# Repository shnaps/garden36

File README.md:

# garden36 🌱

A 36-key wireless split keyboard with Kailh Choc hotswap switches, nice!nano v2 controllers, and nice!view displays.

---

## Features

- **36 keys** — 3×5 column-stagger + 3 thumb keys per half
- **Wireless** — nRF52840 via nice!nano v2, ZMK firmware
- **Hotswap** — Kailh Choc v1 sockets, swap switches without soldering
- **Display** — nice!view MIP display per half (WPM, layer, battery)
- **Battery** — JST-PH LiPo connector + power switch per half
- **Low profile** — Choc spacing, slim build

---

## Gallery

| Top | Bottom |
|-----|--------|
|  |  |

> Photos of the built keyboard coming once V2 is assembled. See `pics/photos/` for updates.

---

## Bill of Materials

Full BOM with source links: [docs/bom.md](docs/bom.md)

| Component | Qty |
|-----------|-----|
| nice!nano v2 | 2 |
| nice!view | 2 |
| Kailh Choc v1 switch | 36 |
| Kailh hotswap socket CPG135001S30 | 36 |
| 1N4148W diode SOD-123 | 36 |
| MSK12C02-HB power switch | 2 |
| B3U-1000P reset button | 2 |
| JST S2B-PH-SM4-TB battery connector | 2 |
| LiPo battery ~110–300 mAh | 2 |
| M2 standoffs + screws | ~28 |
| Choc keycaps | 36 |

---

## PCB

Gerbers and drill files for JLCPCB/PCBWay are in the [latest release](https://github.com/shnaps/garden36/releases/latest).

DXF and SVG edge cuts for laser-cutting plates: [`exports/`](exports/)

---

## Build Guide

Step-by-step assembly instructions: [docs/buildguide.md](docs/buildguide.md)

---

## Firmware

ZMK config: [github.com/shnaps/zmk-config](https://github.com/shnaps/zmk-config)

Flash via UF2 — double-tap reset on each half to enter bootloader, drag-and-drop `.uf2`. See build guide for details.

---

## Case

A **parametric case generator** lives in [`case-gen/`](case-gen/) — it builds
the case (bottom tray, choc switch plate, controller cover) straight from
`garden36.kicad_pcb`, so it always fits the board. Print files in
`case-gen/out/`. See the [case-gen README](case-gen/README.md) for hardware,
parameters, and the in-progress controller-on-bottom redesign.

Older hand-built STEP files remain in [`case/`](case/).

---

## Design History

- **V1** — initial design, 5-column, wired (see [`v1` branch](https://github.com/shnaps/garden36/tree/v1))
- **V2** (current) — redesigned with wireless, nice!view displays, hotswap

---

## Credits

- [marbastlib](https://github.com/ebastler/marbastlib) by ebastler — Choc switch and controller footprints
- [nice!keyboards](https://nicekeyboards.com) — nice!nano and nice!view hardware
- Split keyboard inspiration: [MRIYA](https://github.com/themaxbang/MRIYA), [temper](https://github.com/raeedcho/temper), [urchin](https://github.com/duckyb/urchin)

---

## License

[MIT](LICENSE) © 2025 Viachaslau Ravinski

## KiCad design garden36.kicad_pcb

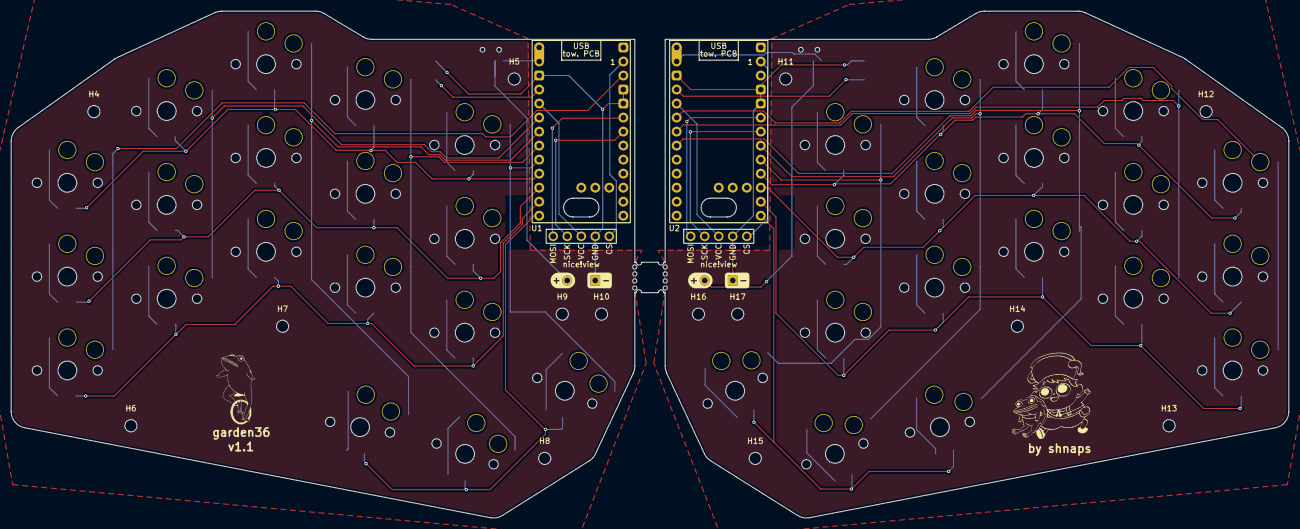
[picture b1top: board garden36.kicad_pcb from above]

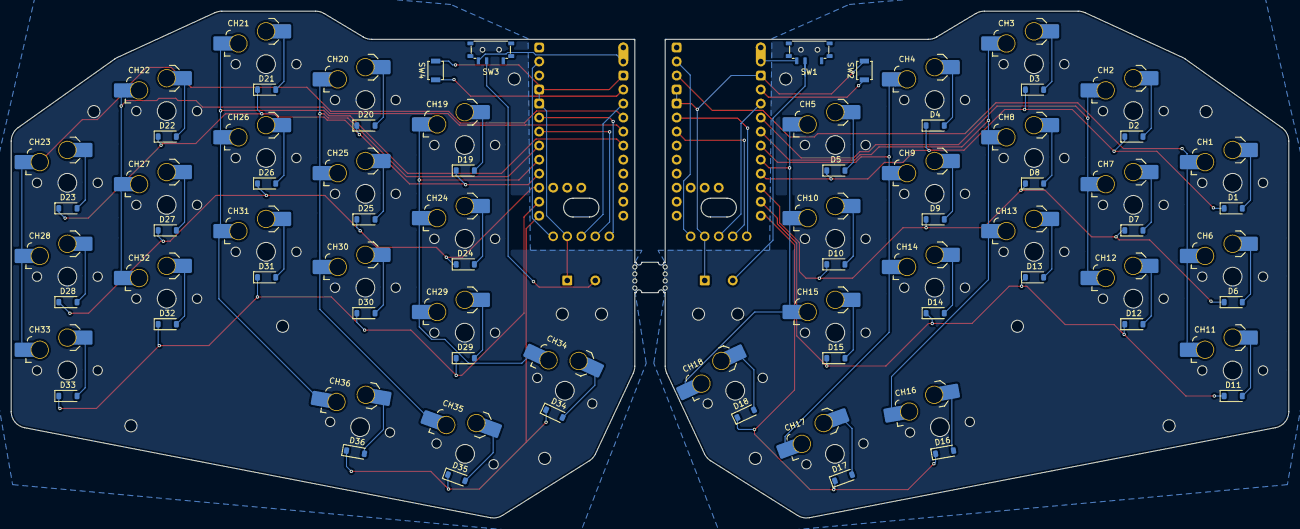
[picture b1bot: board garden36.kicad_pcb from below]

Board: 2 copper layers, 231.5 x 91.8 mm, 100 parts (76 on the bottom side), 70 nets.

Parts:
CH1, CH2, CH3, CH4, CH5, CH6, CH7, CH8, CH9, CH10, CH11, CH12, CH13, CH14, CH15, CH16, CH17, CH18, CH19, CH20, CH21, CH22, CH23, CH24, CH25, CH26, CH27, CH28, CH29, CH30, CH31, CH32, CH33, CH34, CH35, CH36: choc_v1_SW_HS; SW_choc_v1_HS_CPG135001S30_1u
D1, D2, D3, D4, D5, D6, D7, D8, D9, D10, D11, D12, D13, D14, D15, D16, D17, D18, D19, D20, D21, D22, D23, D24, D25, D26, D27, D28, D29, D30, D31, D32, D33, D34, D35, D36: 1N4148W; D_SOD-123
Display1, Display2: nice!view; nice_view
H4, H5, H6, H7, H8, H9, H10, H11, H12, H13, H14, H15, H16, H17: MountingHole; MountingHole_2.2mm_M2
MB4, MB5: mousebites_1mm
PW1, PW2: Battery
SW1, SW3: SW_SPDT; SW_MSK12C02-HB
SW2, SW4: SW_Push; SW_SPST_B3U-1000P
U1, U2: nice_nano; nice_nano_AH_USBdn
by shnaps: LOGO
garden36: LOGO

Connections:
+3.3V: Display1.3 (VCC), U1.16 (3V3)
COL0: CH1.1, CH6.1, CH11.1, U1.2 (P0.08)
COL1: CH2.1, CH7.1, CH12.1, U1.17 (P0.31-LF)
COL2: CH3.1, CH8.1, CH13.1, CH16.1, U1.18 (P0.29-LF)
COL3: CH4.1, CH9.1, CH14.1, CH17.1, U1.19 (P0.02-LF)
COL4: CH5.1, CH10.1, CH15.1, CH18.1, U1.20 (P1.15-LF)
CS: Display1.5 (CS), U1.1 (P0.06)
GND: Display1.4 (GND), PW1.2 (BAT-), SW2.2, U1.3 (GND), U1.4 (GND), U1.14 (GND)
MOSI: Display1.1 (MOSI), U1.5 (P0.17)
unnamed: CH1.2, D1.2 (A)
unnamed: CH2.2, D2.2 (A)
unnamed: CH3.2, D3.2 (A)
unnamed: CH4.2, D4.2 (A)
unnamed: CH5.2, D5.2 (A)
unnamed: CH6.2, D6.2 (A)
unnamed: CH7.2, D7.2 (A)
unnamed: CH8.2, D8.2 (A)
unnamed: CH9.2, D9.2 (A)
unnamed: CH10.2, D10.2 (A)
unnamed: CH11.2, D11.2 (A)
unnamed: CH12.2, D12.2 (A)
unnamed: CH13.2, D13.2 (A)
unnamed: CH14.2, D14.2 (A)
unnamed: CH15.2, D15.2 (A)
unnamed: CH16.2, D16.2 (A)
unnamed: CH17.2, D17.2 (A)
unnamed: CH18.2, D18.2 (A)
unnamed: CH19.2, D19.2 (A)
unnamed: CH20.2, D20.2 (A)
unnamed: CH21.2, D21.2 (A)
unnamed: CH22.2, D22.2 (A)
unnamed: CH23.2, D23.2 (A)
unnamed: CH24.2, D24.2 (A)
unnamed: CH25.2, D25.2 (A)
unnamed: CH26.2, D26.2 (A)
unnamed: CH27.2, D27.2 (A)
unnamed: CH28.2, D28.2 (A)
unnamed: CH29.2, D29.2 (A)
unnamed: CH30.2, D30.2 (A)
unnamed: CH31.2, D31.2 (A)
unnamed: CH32.2, D32.2 (A)
unnamed: CH33.2, D33.2 (A)
unnamed: CH34.2, D34.2 (A)
unnamed: CH35.2, D35.2 (A)
unnamed: CH36.2, D36.2 (A)
unnamed: PW1.1 (BAT+), SW1.2 (B)
unnamed: PW2.1 (BAT+), SW3.2 (B)
RAW: SW1.3 (C), U1.13 (BAT+), U1.29 (BAT+)
ROW0: D1.1 (K), D2.1 (K), D3.1 (K), D4.1 (K), D5.1 (K), U1.21 (P1.13-LF)
ROW1: D6.1 (K), D7.1 (K), D8.1 (K), D9.1 (K), D10.1 (K), U1.22 (P1.11-LF)
ROW2: D11.1 (K), D12.1 (K), D13.1 (K), D14.1 (K), D15.1 (K), U1.23 (P0.10-LF)
ROW3: D16.1 (K), D17.1 (K), D18.1 (K), U1.24 (P0.09-LF)
RST: SW2.1, U1.15 (RST)
R_+3.3V: Display2.3 (VCC), U2.16 (3V3)
R_COL0: CH19.1, CH24.1, CH29.1, CH34.1, U2.8 (P0.24)
R_COL1: CH20.1, CH25.1, CH30.1, CH35.1, U2.7 (P0.22)
R_COL2: CH21.1, CH26.1, CH31.1, CH36.1, U2.19 (P0.02-LF)
R_COL3: CH22.1, CH27.1, CH32.1, U2.18 (P0.29-LF)
R_COL4: CH23.1, CH28.1, CH33.1, U2.17 (P0.31-LF)
R_CS: Display2.5 (CS), U2.1 (P0.06)
R_GND: Display2.4 (GND), PW2.2 (BAT-), SW4.2, U2.3 (GND), U2.4 (GND), U2.14 (GND)
R_MOSI: Display2.1 (MOSI), U2.5 (P0.17)
R_RAW: SW3.3 (C), U2.13 (BAT+), U2.29 (BAT+)
R_ROW0: D19.1 (K), D20.1 (K), D21.1 (K), D22.1 (K), D23.1 (K), U2.9 (P1.00)
R_ROW1: D24.1 (K), D25.1 (K), D26.1 (K), D27.1 (K), D28.1 (K), U2.10 (P0.11)
R_ROW2: D29.1 (K), D30.1 (K), D31.1 (K), D32.1 (K), D33.1 (K), U2.11 (P1.04-LF)
R_ROW3: D34.1 (K), D35.1 (K), D36.1 (K), U2.12 (P1.06-LF)
R_RST: SW4.1, U2.15 (RST)
R_SCK: Display2.2 (SCK), U2.6 (P0.20)
SCK: Display1.2 (SCK), U1.6 (P0.20)

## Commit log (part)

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2025-03-04 Garden36 creation
2025-03-05 Add .gitignore and ready schema
2025-03-05 Ignore #auto_saved_files#
2025-03-06 Move PCB board around
2025-03-06 Remove .lck files from kicad
2025-03-09 Add more ignored files
2025-03-09 Finished basic layout without any routing
2025-03-09 Add v1.1 of buttons and update outline to 0.5mm
2025-03-09 Remove user.1 drawings from kicad
2025-03-10 Add another file to gitgnore
2025-03-10 Finished trace routing for left part
2025-03-11 Add right half of keyboard
2025-03-11 Finished routing for both halfs
2025-03-11 Filled zones for both halfs
2025-05-15 V1 ordered
2025-09-11 V2 started
2025-09-13 Update libraries
2025-09-13 Update libraries continue with updates for project
2025-09-14 Switches set
2025-09-14 Mounting holes for left added
2025-09-15 Add mousebites symbol
2025-09-15 Positioning done
2025-09-15 Start adding routes
2025-09-16 Start connecting to MCU
2025-09-16 Finish design
2025-09-16 Remove jpgs
2025-09-17 V2 ordered
2025-10-03 Add initial drawing for freecad
